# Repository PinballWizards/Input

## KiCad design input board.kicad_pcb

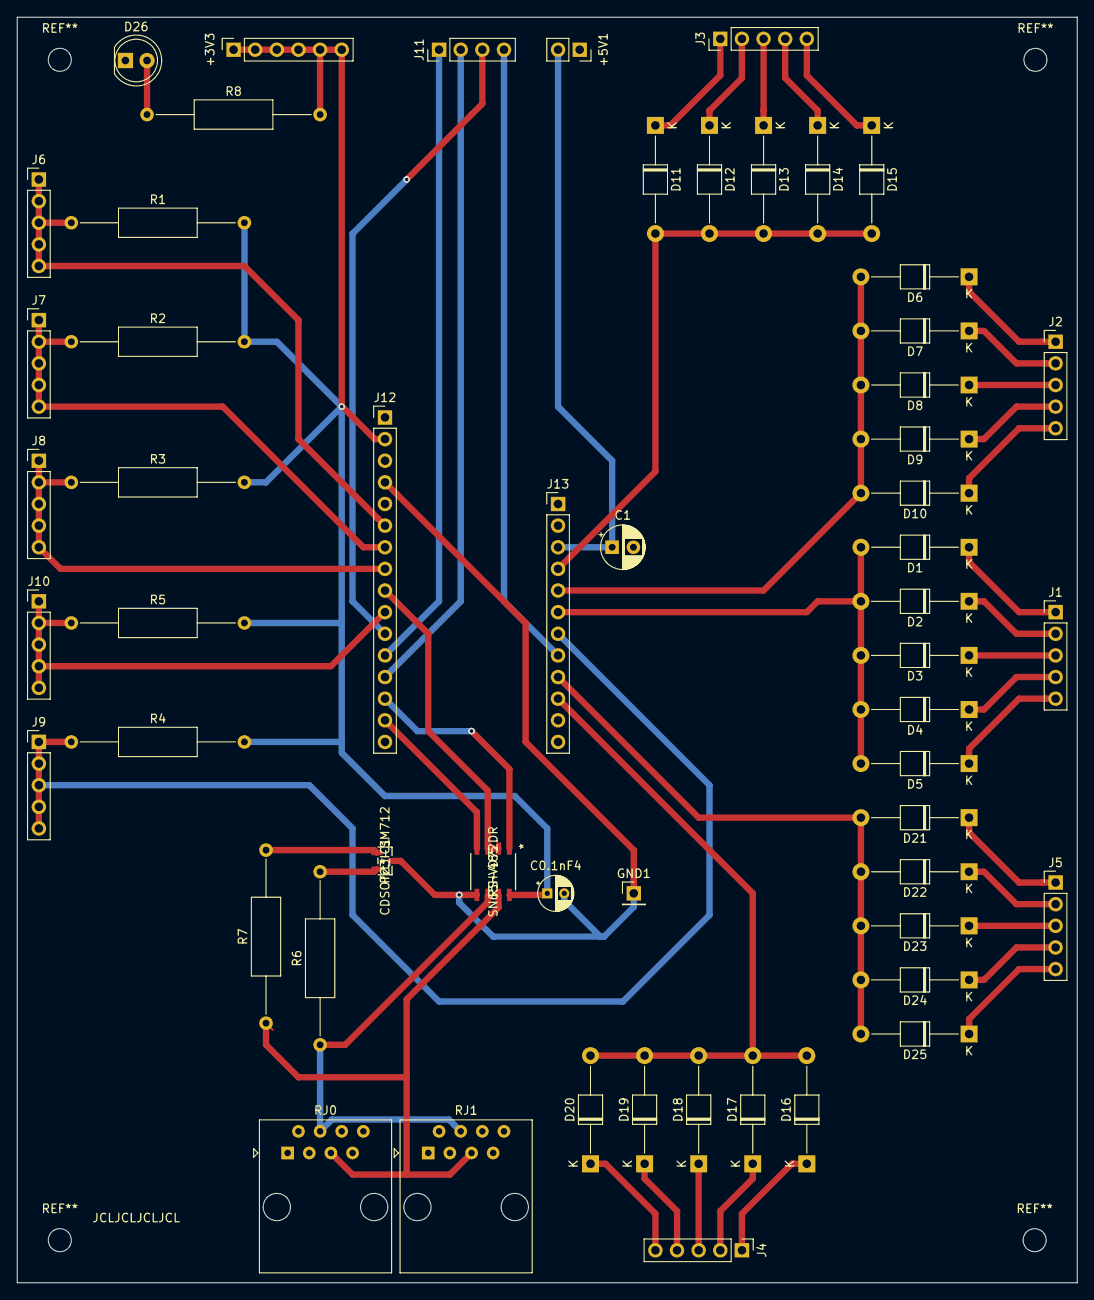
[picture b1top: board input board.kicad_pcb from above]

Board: 2 copper layers, 124.5 x 148.6 mm, 56 parts (0 on the bottom side), 50 nets.

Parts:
+3V3: Conn_01x06_Female; PinSocket_1x06_P2.54mm_Vertical
+5V1: Conn_01x02_Female; PinSocket_1x02_P2.54mm_Vertical
C0.1nF4: 0.1 nF; CP_Radial_D4.0mm_P2.00mm
C1: CP; CP_Radial_D5.0mm_P2.50mm
D1, D2, D3, D4, D5, D6, D7, D8, D9, D10, D11, D12, D13, D14, D15, D16, D17, D18, D19, D20, D21, D22, D23, D24, D25: DIODE; D_T-1_P12.70mm_Horizontal
D26: LED; LED_D5.0mm
GND1: Conn_01x01_Male; PinHeader_1x01_P2.54mm_Vertical
J1, J2, J3, J4, J5, J6, J7, J8, J9, J10: Conn_01x05_Female; PinHeader_1x05_P2.54mm_Vertical
J11: Conn_01x04_Female; PinHeader_1x04_P2.54mm_Vertical
J12: MCU_LEFT_LEGS; PinHeader_1x16_P2.54mm_Vertical
J13: MCU_RIGHT_LEGS; PinHeader_1x12_P2.54mm_Vertical
Prt_IC1: CDSOT23-SM712
R1, R2, R3, R4, R5: 10k; R_Axial_DIN0309_L9.0mm_D3.2mm_P20.32mm_Horizontal
R6: R10; R_Axial_DIN0309_L9.0mm_D3.2mm_P20.32mm_Horizontal
R7: R11; R_Axial_DIN0309_L9.0mm_D3.2mm_P20.32mm_Horizontal
R8: 470; R_Axial_DIN0309_L9.0mm_D3.2mm_P20.32mm_Horizontal
RJ0, RJ1: RJ45; RJ45_Amphenol_54602-x08_Horizontal
RS-485: SN65HVD72DR

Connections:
+3V3: +3V3.1, +3V3.2, +3V3.3, +3V3.4, +3V3.5, +3V3.6, C0.1nF4.1, J12.2, R1.2, R2.2, R3.2, R4.2, R5.2, R8.2, RS-485.8
+5V: +5V1.2, C1.1, J13.3
/A1: J6.1, J6.2, J6.3, J6.4, J6.5, J12.6, R1.1
/A2: J7.1, J7.2, J7.3, J7.4, J7.5, J12.7, R2.1
/A3: J8.1, J8.2, J8.3, J8.4, J8.5, J12.8, R3.1
/A4: J12.9, RS-485.2, RS-485.3
/A5: J10.1, J10.2, J10.3, J10.4, J10.5, J12.10, R5.1
/D5: D16.2, D17.2, D18.2, D19.2, D20.2, J13.10
/D6: D21.2, D22.2, D23.2, D24.2, D25.2, J13.9
/D9: J11.4, J13.8
/D10: J9.1, J9.2, J9.3, J9.4, J9.5, J13.7, R4.1
/D11: D1.2, D2.2, D3.2, D4.2, D5.2, J13.6
/D12: D6.2, D7.2, D8.2, D9.2, D10.2, J13.5
/D13: D11.2, D12.2, D13.2, D14.2, D15.2, J13.4
/MISO: J11.2, J12.13
/MOSI: J11.1, J12.12
/RJ45_4: R6.1, RJ0.4, RJ1.4, RS-485.6
/RJ45_5: R7.1, RJ0.5, RJ1.5, RS-485.7
/RXO: J12.14, RS-485.1
/SCK: J11.3, J12.11
/TX1: J12.15, RS-485.4
GND: +5V1.1, C0.1nF4.2, C1.2, D26.1, GND1.1, J12.4, J12.16, Prt_IC1.3, RS-485.5
unnamed: D1.1, J1.1
unnamed: D2.1, J1.2
unnamed: D3.1, J1.3
unnamed: D4.1, J1.4
unnamed: D5.1, J1.5
unnamed: D6.1, J2.1
unnamed: D7.1, J2.2
unnamed: D8.1, J2.3
unnamed: D9.1, J2.4
unnamed: D10.1, J2.5
unnamed: D11.1, J3.1
unnamed: D12.1, J3.2
unnamed: D13.1, J3.3
unnamed: D14.1, J3.4
unnamed: D15.1, J3.5
unnamed: D16.1, J4.1
unnamed: D17.1, J4.2
unnamed: D18.1, J4.3
unnamed: D19.1, J4.4
unnamed: D20.1, J4.5
unnamed: D21.1, J5.1
unnamed: D22.1, J5.2
unnamed: D23.1, J5.3
unnamed: D24.1, J5.4
unnamed: D25.1, J5.5
unnamed: D26.2, R8.1
unnamed: Prt_IC1.1, R7.2
unnamed: Prt_IC1.2, R6.2

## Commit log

2020-02-24 PCB and Gerber files
2020-02-25 BOM update
2020-02-27 Update mounting holes and ground plane
2020-03-05 Update switch matrix on input board schematic
2020-03-06 Updated PCB and gbr files

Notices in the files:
parts and their libraries:
Copyright 2016 Accelerated Designs. All rights reserved.
